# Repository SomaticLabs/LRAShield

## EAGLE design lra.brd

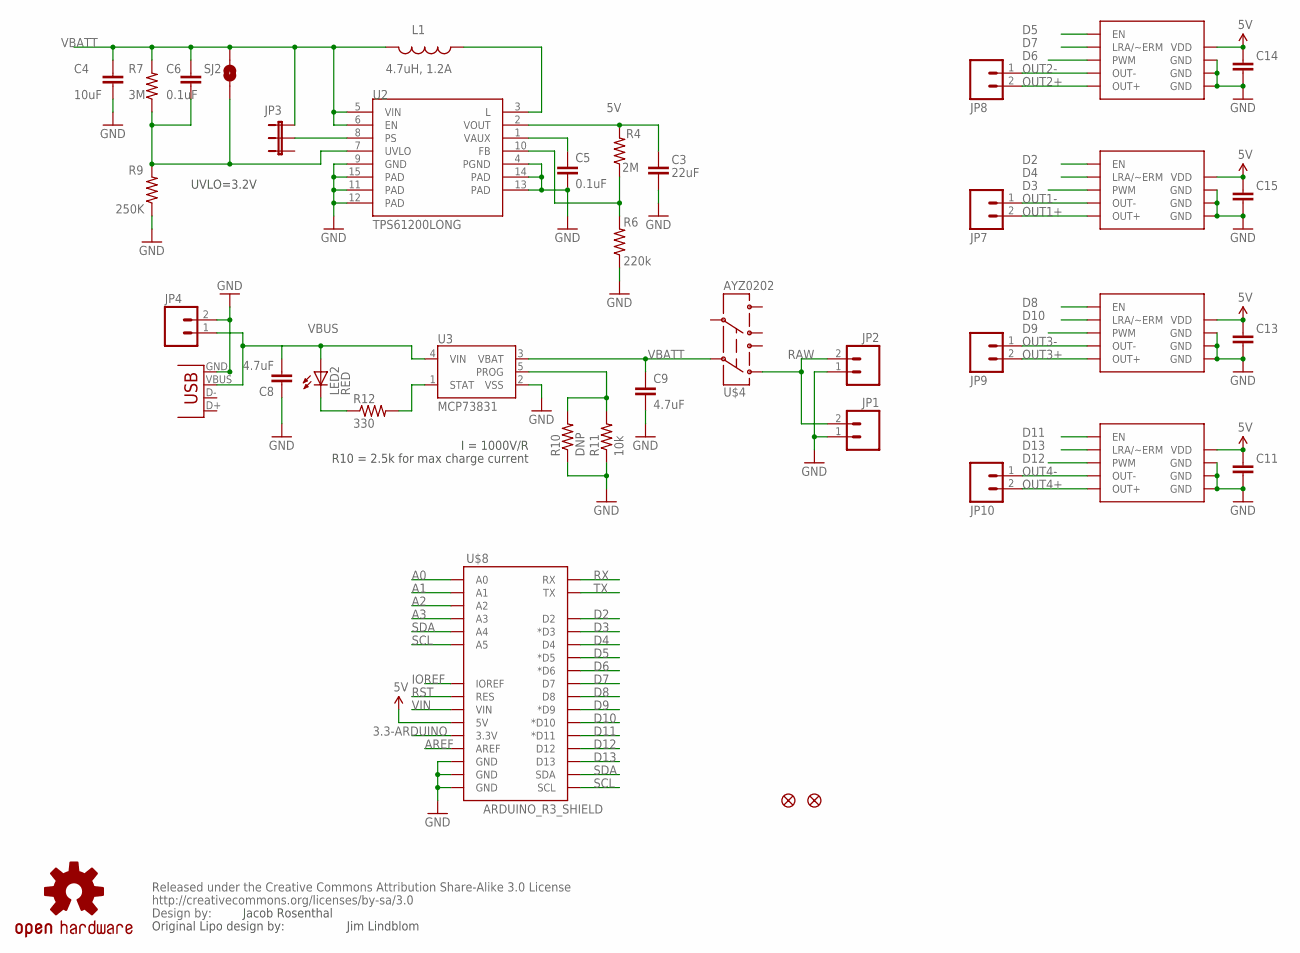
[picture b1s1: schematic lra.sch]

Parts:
$$U$1: CREATIVE_COMMONS
C3: 22uF; 0805
C4: 10uF; 0805
C5, C6: 0.1uF; 0805
C8, C9: 4.7uF; 0805
C11, C13, C14, C15: CAP0805; 0805
JP1, JP4: M021X02_NO_SILK; 1X02_NO_SILK
JP2: M02-JST-2MM-SMT; JST-2-SMD
JP3: JUMPER-32-3; SJ_3_PASTE2&3
JP5, JP6: FIDUCIAL1X2.5; FIDUCIAL-1X2.5
JP7, JP8, JP9, JP10: M02PTH3; 1X02_LONGPADS
L1: 4.7uH, 1.2A; CDRH2D09
LED2: RED; CHIP-LED0805
R4: 2M; 0805
R6: 220k; 0805
R7: 3M; 0805
R9: 250K; 0805
R10: DNP; 0805
R11: 10k; 0805
R12: 330; 0805
SJ2: Power Saving Off; SJ_2S-NO
U2: TPS61200LONG; QFN-10_PAD_LONG
U3: MCP73831; SOT23-5
U$2, U$3, U$6: DRV260310WFQFN; 10WFQFN
U$4: AYZ0202
U$7: DRV2603; 10WFQFN-LONG
U$8: ARDUINO_R3_SHIELD; UNO_R3_SHIELD
U$100: OSHW-LOGOM; OSHW-LOGO-M
X1: USBSMD; USB-MINIB

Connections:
3.3-ARDUINO: U$8.3.3V
5V: C3.1, C11.1, C13.1, C14.1, C15.1, R4.2, U2.2 (VOUT), U$2.P$7 (VDD), U$3.P$7 (VDD), U$6.P$7 (VDD), U$7.P$7 (VDD), U$8.5V
A0: U$8.A0
A1: U$8.A1
A2: U$8.A2
A3: U$8.A3
AREF: U$8.AREF
D2: U$3.P$1 (EN), U$8.D2
D3: U$3.P$2 (PWM), U$8.D3 (*D3)
D4: U$3.P$3 (LRA/~ERM), U$8.D4
D5: U$2.P$1 (EN), U$8.D5 (*D5)
D6: U$2.P$2 (PWM), U$8.D6 (*D6)
D7: U$2.P$3 (LRA/~ERM), U$8.D7
D8: U$6.P$1 (EN), U$8.D8
D9: U$6.P$2 (PWM), U$8.D9 (*D9)
D10: U$6.P$3 (LRA/~ERM), U$8.D10 (*D10)
D11: U$7.P$1 (EN), U$8.D11 (*D11)
D12: U$7.P$2 (PWM), U$8.D12
D13: U$7.P$3 (LRA/~ERM), U$8.D13
FB: R4.1, R6.2, U2.10 (FB)
GND: C3.2, C4.2, C5.2, C8.1, C9.2, C11.2, C13.2, C14.2, C15.2, JP1.1, JP2.1, JP4.2, R6.1, R9.1, R10.1, R11.1, U2.4 (PGND), U2.9 (GND), U2.11 (PAD), U2.12 (PAD), U2.13 (PAD), U2.14 (PAD), U2.15 (PAD), U3.2 (VSS), U$2.GND@1 (GND), U$2.GND@2 (GND), U$2.GND@3 (GND), U$3.GND@1 (GND), U$3.GND@2 (GND), U$3.GND@3 (GND), U$6.GND@1 (GND), U$6.GND@2 (GND), U$6.GND@3 (GND), U$7.GND@1 (GND), U$7.GND@2 (GND), U$7.GND@3 (GND), U$8.GND@0 (GND), U$8.GND@1 (GND), U$8.GND@2 (GND), X1.GND
IOREF: U$8.IOREF
unnamed: L1.P$1 (1), U2.3 (L)
unnamed: C5.1, U2.1 (VAUX)
unnamed: LED2.C, R12.1
OUT1+: JP7.2, U$3.P$9 (OUT+)
OUT1-: JP7.1, U$3.P$6 (OUT-)
OUT2+: JP8.2, U$2.P$9 (OUT+)
OUT2-: JP8.1, U$2.P$6 (OUT-)
OUT3+: JP9.2, U$6.P$9 (OUT+)
OUT3-: JP9.1, U$6.P$6 (OUT-)
OUT4+: JP10.2, U$7.P$9 (OUT+)
OUT4-: JP10.1, U$7.P$6 (OUT-)
PROG: R10.2, R11.2, U3.5 (PROG)
PS: JP3.2, U2.8 (PS)
RAW: JP1.2, JP2.2, U$4.3 (1)
RST: U$8.RES
RX: U$8.RX
SCL: U$8.A5, U$8.SCL
SDA: U$8.A4, U$8.SDA
STAT: R12.2, U3.1 (STAT)
TX: U$8.TX
UVLO: C6.2, R7.1, R9.2, SJ2.1, U2.7 (UVLO)
VBATT: C4.1, C6.1, C9.1, JP3.3, L1.P$2 (2), R7.2, SJ2.2, U2.5 (VIN), U2.6 (EN), U3.3 (VBAT), U$4.2
VBUS: C8.2, JP4.1, LED2.A, U3.4 (VIN), X1.VBUS
VIN: U$8.VIN

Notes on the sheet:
Jacob Rosenthal
I = 1000V/R
R10 = 2.5k for max charge current
UVLO=3.2V
Original Lipo design by:
Jim Lindblom

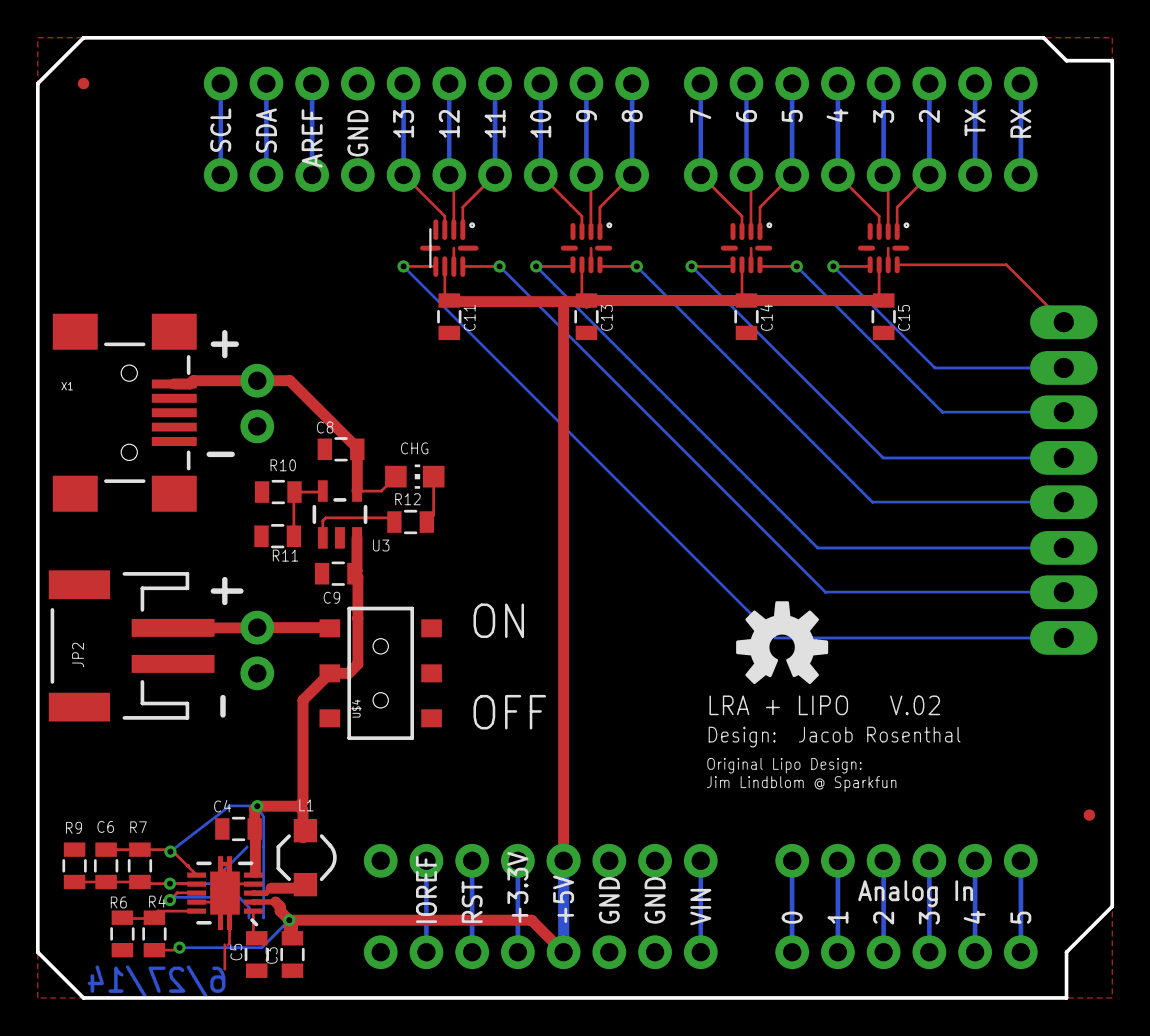
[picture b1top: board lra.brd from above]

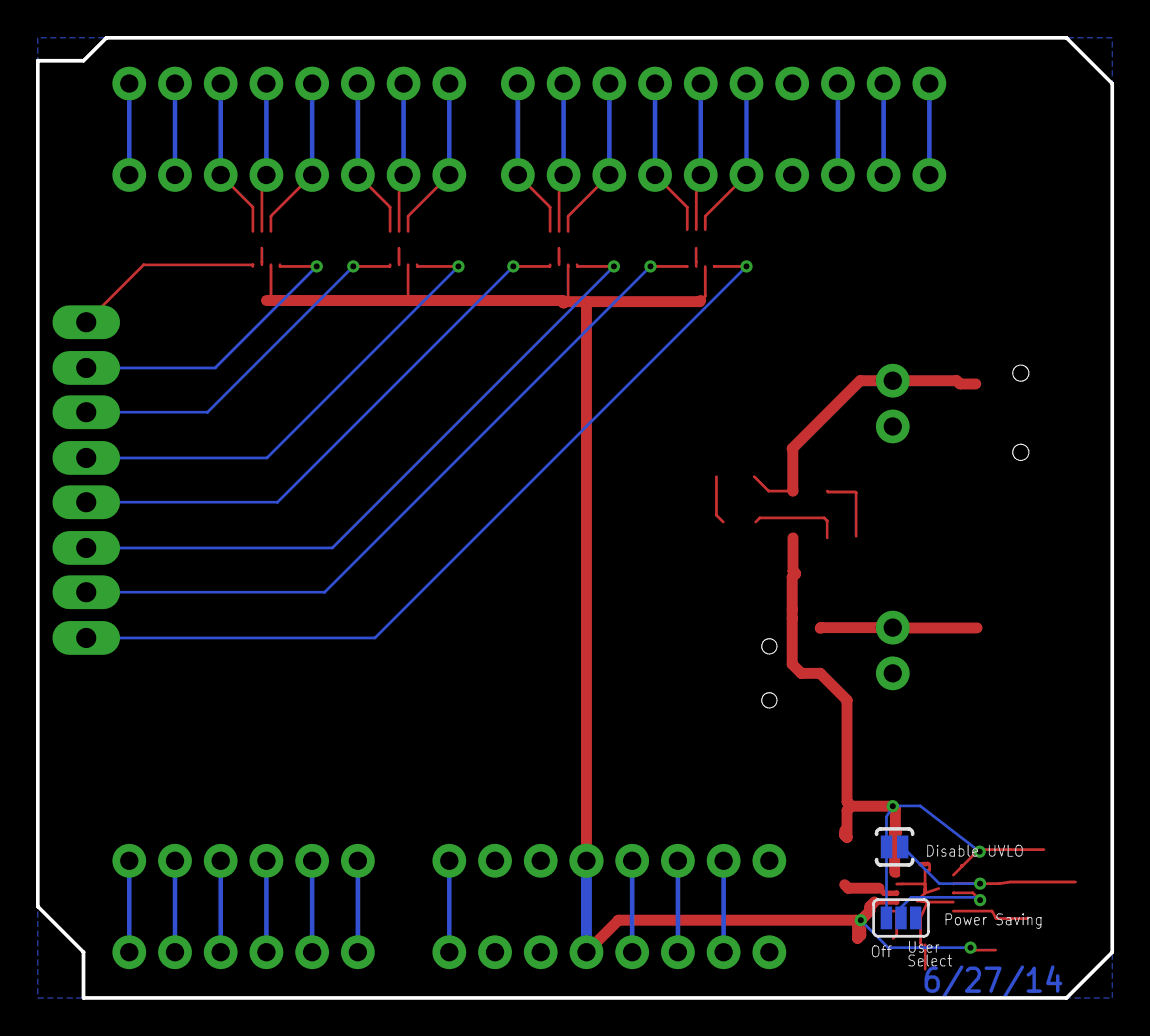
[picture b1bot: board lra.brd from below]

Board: 2 copper layers, 59.7 x 53.3 mm, 41 parts (2 on the bottom side), 35 nets.

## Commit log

2014-06-28 v.01
2014-06-28 v.02
